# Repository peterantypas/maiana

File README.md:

# MAIANA&trade;: The Open Source AIS Transponder

I started this project around 2015 with the intention of experimenting and eventually building something for my own boat.
I was not impressed with commercial AIS class B transponders. They seemed bloated, expensive and some of them were particularly power-hungry. Also, my boat is rather small and I have very little room for "nav" instruments, so I didn't want a huge enclosure inside plus two external RF cables, one for VHF and one for GPS. So I set out to create my own "lean and mean" design and I sailed with it for 2 years.

Fast forward to 2023, and it has taken a life of its own:

The main difference between MAIANA&trade; and every commercial transponder is that it's a self-contained unit, and thus its performance is 100% repeatable. The entire transponder circuit, the GNSS and all antennas are in the same housing. The design has been validated by fabricating _over 300 units_ now (July 2023).

So with all the core functionality kept outside and under tight control, the only other thing we need is power and data connections. Now, what's the most common cable that can carry a few signals 50 feet away? If you guessed "Ethernet", you guessed right. Commonplace Cat5 cable can deliver power plus serial data signals anywhere on an average sized pleasure boat. So that's how the exterior unit connects to the cabin, where one of these breakouts offers USB, NMEA0183 or NMEA2000 adapters to connect to the rest of the boat's systems. 

## Hardware Design

### Mechanical
The antenna casing that you see in these photos is a piece of 1" Schedule 40 "furniture" grade PVC pipe. It is the highest grade of such material, with a solid white PVC core (not a coated household grade pipe). Still, it's the most inexpensive UV resistant material available, and it looks great too!

The VHF antenna whip is built using an epoxy wound filament tube coated with high quality, UV resistant irradiated polyolefin ("heat shrink"). The company that makes this tubing (and helped me with this design challenge) also built the landing gear for NASA's Ingenuity helicopter on Mars, so they definitely understand how to deal with harsh environments. The bottomline is that unlike typical fiberglass antenna masts, this antenna is not going to degrade and "blossom" under continuous UV exposure. Starting with January of 2022, the antenna tube will be made of two telescopic pieces of the same material. This will greatly reduce the cost of shipping the kit to Europe and Australia.

The entire outdoor assembly is held together by the same high grade heat shrink tubing, so there is no need for any adhesives! The main water seal is formed by heat shrinking around a specially designed 3D printed cap made of PLA. This part naturally softens when heated and as it's compressed by the heat shrink tubing surrounding it, it forms a permanent, watertight colar around the antenna tube. This blocks rain water and salt spray from the top. A layer of clear heat shrink in the interior forms a secondary water seal encompassing the lower part of the antenna. Finally, the PCB can be sprayed with conformal coating for an added layer of protection. Silicone spray works best and has no appreciable detuning effect on the GNSS.

With no adhesives getting in the way, the unit can actually be opened and serviced by (carefully) cutting through the heat shrink tubing with a knife, then resealing with the same material and method as before. This, in fact, was one of my design goals from the beginning.

### Electrical
As I mentioned already, the transponder circuit is inside the antenna case. It's a 24mm x 84mm 4-layer PCB:

The core design is based on two Silicon Labs "EZRadio Pro" series ICs. All kits shipping today are based on the Si4460.

The microcontroller on this board is a STM32L4 series (422, 431 and 432 supported). I chose these because the 80MHz clock allows the SPI bus to operate at exactly 10MHz which is the maximum supported by the Si446x ICs. This is important, as a transponder is a *hard real time* application, so SPI latency must be minimized. All kits today are based on the STM32L432KBU6.

The GNSS is now a Quectel L76L-M33 and relies on a Johansson ceramic chip antenna. It usually takes a minute to acquire a fix outdoors from a cold start. With the latest antenna tuning, it offers near-navigation grade accuracy (typical HDOP at sea is less than 2 meters).

The transmitter front end is based on a power MOSFET typically found in handheld VHF radios and outputs just over 2 Watts (+33dBm). It has a verified range of over 20 nautical miles on a masthead and 10+ miles on a pushpit.

The system is designed to run from a 12V battery and exposes a 3.3V-level UART for connecting to the rest of the boat. The UART continuously sends GPS and AIS data in NMEA0183 format at 38.4Kbps. It also accepts certain commands for management. The breakout boxes pictured above deliver this stream via USB, NME0183 (RS422) or NMEA 2000 (CAN). The 3 "fancy" breakouts feature _galvanic isolation_ of their USB connection to avoid causing unintended problems with laptops and other devices whose power supplies are meant to _float_. This also means that you cannot use USB to power MAIANA&trade; - it must connect to a 12V battery.

In addition, there is now a "bare bones" UART+USB breakout:

This provides the simplest, lowest cost interface to a Raspberry Pi, Arduino or any other similar system you may want to wire directly. It is _not_ galvanically isolated to keep the cost really low. This adapter is now part of the base kit and ships with every configuration.

For the circuit to transmit, it must be configured with persistent station data (MMSI, call sign, name, dimensions, etc). This is stored in an EEPROM and is provisioned over a USB/serial connection via a command line interface. If station data is not provisioned, the device will simply run as a 2 channel AIS + GNSS receiver.

SOTDMA synchronization is based on the very acurate 1 PPS signal from the GNSS and the UTC clock. MAIANA&trade; does not synchronize itself to other stations because practical experience revealed that it's literally the "Wild West" out there: There are *many* commercial class A systems in operation today with buggy time slot management, so the simplest solution is to not rely on any of them. That said, the design behaves as a "class B" so it will not attempt to reserve time slots. It will just transmit autonomously and independently, based on Clear Channel Assessment, at the schedule permitted for this class of device. 

All adapters (except the "bare bones" one) feature a *silent mode* switch to explicitly disable transmission. If you need this for the UART adapter, you can wire one yourself.

In terms of power consumption, the main board draws about 45mA from 12V in receive mode, and spikes up to 700mA during transmission (for only 27 milliseconds). The adapters add an extra 0.5mA - 25mA depending on choice. So MAIANA&trade;'s most power hungry configuration needs about 0.6 Watts, which is a lot less than a typical LED-based cabin light.

### Software

The transponder firmware is an [Eclipse CDT project](latest/Firmware/Transponder) that you could clone and build. The code is C++ with a BSP abstraction layer so you need to tweak bsp/bsp.hpp or define one of the required symbols in the preprocessor to build for different board revisions. It contains snippets of STM32Cube generated code, but is does not follow ST's "spaghetti" structure.

The NMEA2000 adapter also has its own separate [firmware project](latest/Firmware/NMEA2000Adapter).

As of December 2021, MAIANA&trade; is fully integrated into [OpenPlotter](https://openmarine.net/openplotter). This means that it can be provisioned and managed entirely from its graphical interface, including firmware updates. To accomplish this, I had to make both a hardware and a software change: 

- The hardware change was to reinstate the I2C EEPROM that I used in earlier designs. This was necessary because STM32 applications that are interrupt heavy cannot safely erase and write any pages in the same flash bank, as the *entire* bank gets locked. This means that the next interrupt may be unable to execute, thus causing the processor to hang until the watchdog resets it. Moving persistence to an EEPROM solves this problem.

- The software change was to dust off the original [bootloader](latest/Firmware/Bootloader) that I wrote years ago and make it bulletproof: Even if you manage to brick the unit by uploading garbage firmware into it, it has a built-in "rescue" mode. All you have to do is toggle the TX switch a couple of times during the first 2 seconds after power-up and it will enter firmware update mode again.

### CAD

Everything is [here](latest/CAD). 

### Building the unit

This is going to be difficult for all but the most technically advanced. The board features all surface mounted components, with 4 QFNs, a few SOT-363s and tightly spaced 0603 passives. The antenna switch on board 11.3.0 is about 0.8 x 1 mm and you'll need a microscope to align it. So unless you're very skilled and well equipped, you will find it difficult to build. 

### Buying a kit

I have developed a kit which includes pre-soldered (and programmed) boards as well as the antenna, main casing and heat shrink tubing. See [the installation manual here](https://github.com/peterantypas/maiana/blob/master/latest/Manuals/MAIANA%E2%84%A2%20Assembly%20Manual%20(Rev%204).pdf) to get a better idea of the process.

If you are located in North America, send an email to *maiana.kits@_dontspam_gmail.com* (remove the spambot blocker of course). Tariffs have made it difficult to ship to Europe and vice versa, so [OpenMarine](https://shop.openmarine.net) is working with European based teams to build and ship directly from Barcelona, Spain.

### License

CAD and transponder firmware are licensed under GPLV3. I chose the most "copyleft" license to discourage commercial entities from ripping this off and then "close-sourcing" it. The flipside of this is that if you can fork the design and make something better, then you deserve the success! That said, MAIANA&trade; will become a registered trademark soon, so if you plan to do this you must use a different name.

The NMEA2000 adapter firmware is under MIT license to be consistent with the libraries it depends on. Feel free to use it as you wish.

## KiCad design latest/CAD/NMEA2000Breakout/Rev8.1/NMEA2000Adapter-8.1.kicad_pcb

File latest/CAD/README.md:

## Board design files

This directory contains Eagle CAD files as well as schematic PDFs and Gerber exports for board fabrication.

The board stackup is good enough for either OSH Park 4-layer, or JLCPCB 4-layer with controlled impedance (JLC2313). 

### Latest Board

Revision 11.5.2 does away with the (hard to source) regulator from ST and replaces it with a Zener + NPN combination that delivers about 8.5V to the PA under load.

### Breakouts
These directories contain Eagle and FreeCAD files for the NMEA0183, NMEA 2000 and USB adapters. Their front panels are PCBs so gerbers are
here as well. The UART+USB adapter is a very basic breakout board for those who would rather wire the transponder themselves.

### Antenna
This directory contains FreeCAD and STEP exports of the 3D printed parts that make up the antenna.

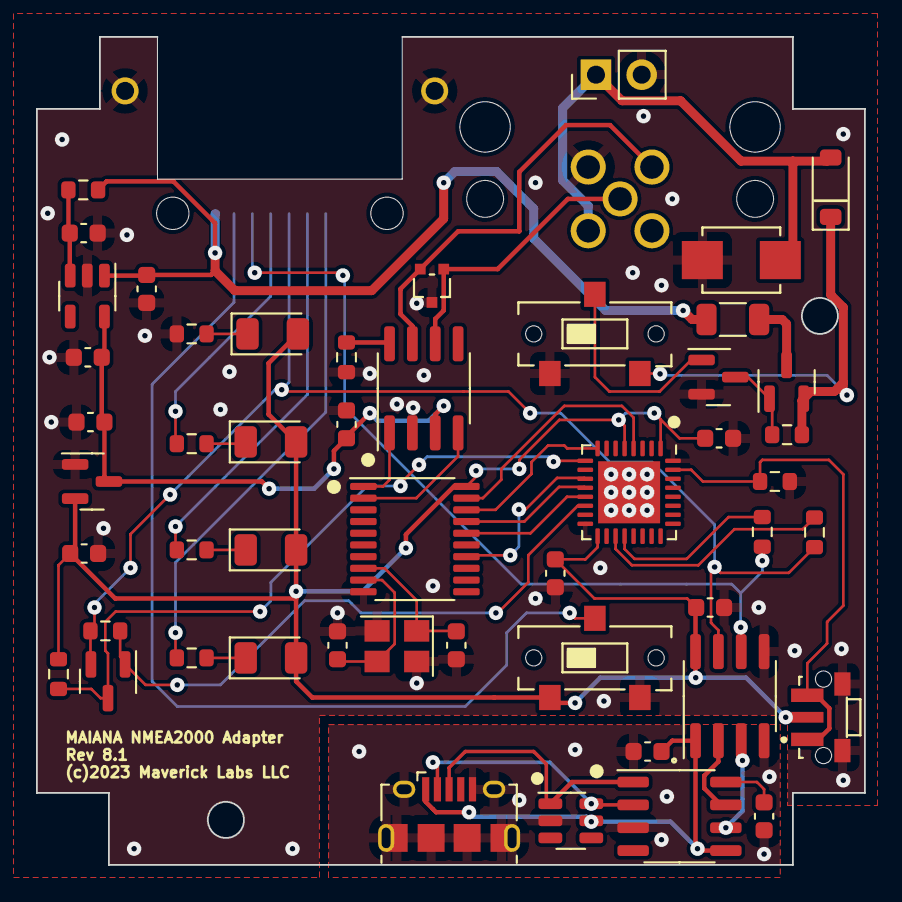
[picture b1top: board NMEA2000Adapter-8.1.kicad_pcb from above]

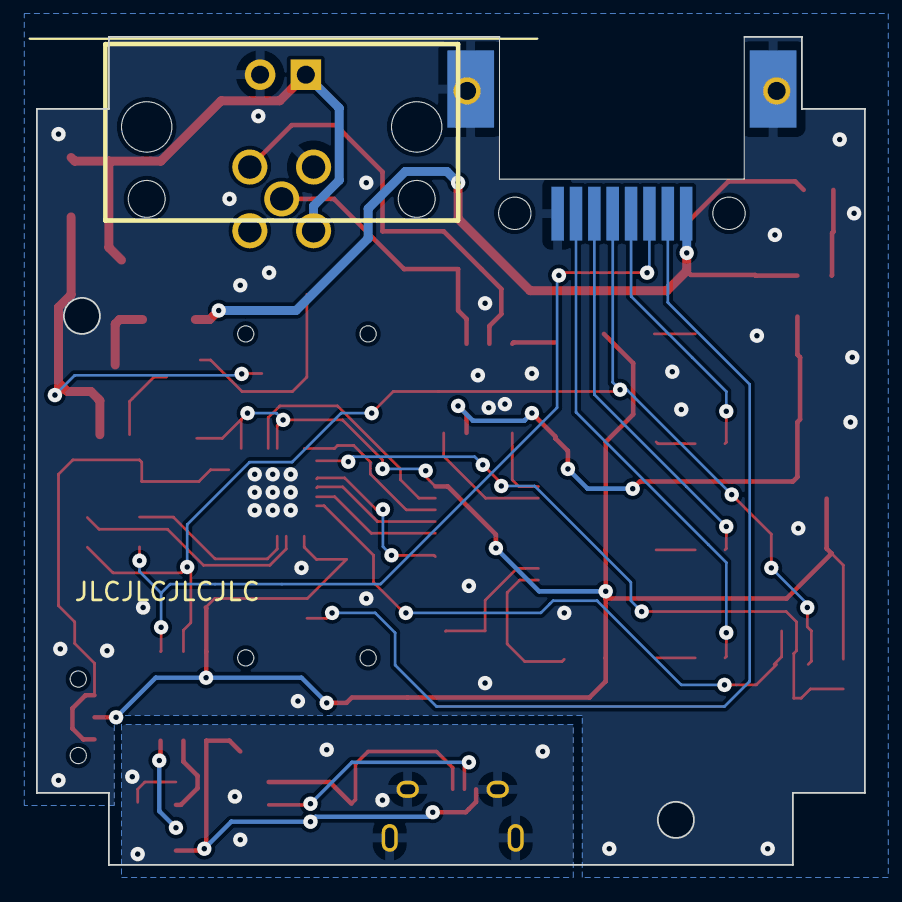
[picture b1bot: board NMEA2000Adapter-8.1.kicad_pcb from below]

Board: 2 copper layers, 46.0 x 46.0 mm, 52 parts (2 on the bottom side), 44 nets.

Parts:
C1, C2, C3, C11, C12, C13: 0.1uF; C_0603_1608Metric
C4, C5: 20pF; C_0603_1608Metric
C6, C7, C8, C9, C10: 1uF; C_0603_1608Metric
D1, D2, D3, D4: LED; LED_1206_3216Metric
D5: PESD1CAN-U; SOT323
D6: SMBJ16CA; DIOM4336X265N
D8: D_Schottky; D_SOD-123
J1: 12-3701-05; MICRO_C_5PIN
J2: RJ-82A86MMNL
J3: USB_B_Micro; USB_Micro-B_Amphenol_10118194_Horizontal
J4: Conn_01x02; PinHeader_1x02_P2.54mm_Vertical
Q1, Q3: BSS138; SOT-23
Q2: AO3401A; SOT-23
R1, R2, R3, R4: 2k2; R_0603_1608Metric
R5, R6, R7, R8, R9, R10: 10k; R_0603_1608Metric
R11, R12: 0R; R_0603_1608Metric
SW1, SW2: CL-SB-12B-01T
SW3: TS-1814; TE_1977066-1
TH1: BSMD1206-050-16V; R_1206_3216Metric
U1: STM32L432KBUx; QFN-32-1EP_5x5mm_P0.5mm_EP3.45x3.45mm
U2: MCP2515-xST; TSSOP-20_4.4x6.5mm_P0.65mm
U3: MCP2551-I-SN; SOIC-8_3.9x4.9mm_P1.27mm
U4: SRV05-4; SOT-23-6
U5: CH340N; SO-8_3.9x4.9mm_P1.27mm
U6: ISO7721DR; SOIC-8_3.9x4.9mm_P1.27mm
U7: TJ5205SF5-5.0; SOT-23-5
U8: SE8533X2-HF; SOT-23
Y1: X322516MOB4SI; Crystal_SMD_3225-4Pin_3.2x2.5mm

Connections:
+3.3V: C2.1, C10.1, C12.1, C13.1, D1.2 (A), D2.2 (A), D3.2 (A), D4.2 (A), R10.1, SW2.1, SW3.2, U1.1 (VDD), U1.5 (VDDA), U1.17 (VDD), U2.20 (VDD), U6.8 (VDD2), U8.2 (VO)
+5V: C8.1, C9.1, C11.1, U3.3 (VDD), U7.5 (OUT), U8.3 (VI)
+12V: D6.2, D8.2 (A), J1.2, J4.1
/CAN/CAN_H: D5.2, J1.4, U3.7 (CANH)
/CAN/CAN_L: D5.1, J1.5, U3.6 (CANL)
/CAN/NRST: U1.4 (NRST), U2.19 (~RESET)
/CAN/SPI_CS: U1.8 (PA2), U2.18 (~CS)
/CAN/SPI_MISO: U1.12 (PA6), U2.17 (SO)
/CAN/SPI_MOSI: U1.13 (PA7), U2.16 (SI)
/CAN/SPI_SCK: U1.11 (PA5), U2.14 (SCK)
/Connections/AIS_RX_EVENT: J2.P$6 (6), R3.2
/Connections/AIS_TX_EVENT: J2.P$7 (7), R4.2
/Connections/GPS_STATUS: J2.P$4 (4), R2.2
/Connections/MCU_UART_RX: R12.2, U1.20 (PA10)
/Connections/MCU_UART_TX: R11.2, U1.19 (PA9)
/Connections/TRANSPONDER_UART_TX: J2.P$5 (5), Q3.2 (S), R9.2, R11.1, U6.7 (VIA)
/Connections/TX_DISABLE: J2.P$2 (2), SW2.C
/Connections/V_OUT: C7.1, J2.P$1 (1), R6.1, TH1.1, U7.1 (IN)
/MCU/BOOT0: R8.1, SW3.1, SW3.3, U1.31 (PH3)
/Power/PWR_CTRL: Q1.1 (G), SW1.C
/Power/V_IN: D8.1 (K), Q2.2 (S), R5.1, SW1.3
CH340_RX: U5.7 (RX), U6.2 (VOA)
CH340_TX: U5.6 (TX), U6.3 (VIB)
D+: J3.3 (D+), U4.1 (IO1), U5.1 (D+)
D-: J3.2 (D-), U4.6 (IO4), U5.2 (D-)
GND: C2.2, C4.2, C5.2, C6.2, C7.2, C8.2, C9.2, C10.2, C11.2, C12.2, C13.2, D5.3, D6.1, J1.3, J2.P$8 (8), J2.P$9, J2.P$10, J2.P$11, J2.P$12, J4.2, Q1.2 (S), R1.2, R7.2, R8.2, SW1.1, SW2.3, SW3.S1 (SHIELD), SW3.S2 (SHIELD), U1.16 (VSS), U1.32 (VSS), U1.33 (VSS), U2.10 (VSS), U3.2 (VSS), U6.5 (GND2), U7.2 (GND), U8.1 (GND), Y1.2, Y1.4
GND2: C1.2, C3.2, J3.5 (GND), J3.6 (Shield), U4.2 (VN), U5.3 (GND), U6.4 (GND1)
NMEA_RX: Q3.3 (D), R10.2, U1.9 (PA3)
NMEA_RX_EN: Q3.1 (G), R9.1, U1.14 (PB0)
unnamed: D1.1 (K), R1.1
unnamed: D2.1 (K), R2.1
unnamed: D3.1 (K), R3.1
unnamed: D4.1 (K), R4.1
unnamed: Q1.3 (D), Q2.1 (G), R5.2
unnamed: Q2.3 (D), TH1.2
unnamed: U2.2 (RXCAN), U3.4 (RXD)
unnamed: U2.1 (TXCAN), U3.1 (TXD)
unnamed: R7.1, U3.8 (Rs)
unnamed: C1.1, U5.8 (V3)
unnamed: C6.1, R6.2, U7.3 (EN)
TRANSPONDER_UART_RX: J2.P$3 (3), R12.1, U6.6 (VOB)
VBUS: C3.1, J3.1 (VBUS), U4.5 (VP), U5.5 (VCC), U6.1 (VDD1)
XTL1: C5.1, U2.8 (OSC2), Y1.1
XTL2: C4.1, U2.9 (OSC1), Y1.3

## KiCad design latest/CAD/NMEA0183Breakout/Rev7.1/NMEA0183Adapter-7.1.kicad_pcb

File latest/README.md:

## This is the current version

This folder contains the latest and greatest. Under CAD/, you'll find directories for each board revision with associated Eagle files and exports. 

Under Firmware/ you'll find two Eclipse CDT projects. One for the transponder, and one for the NMEA 2000 adapter.

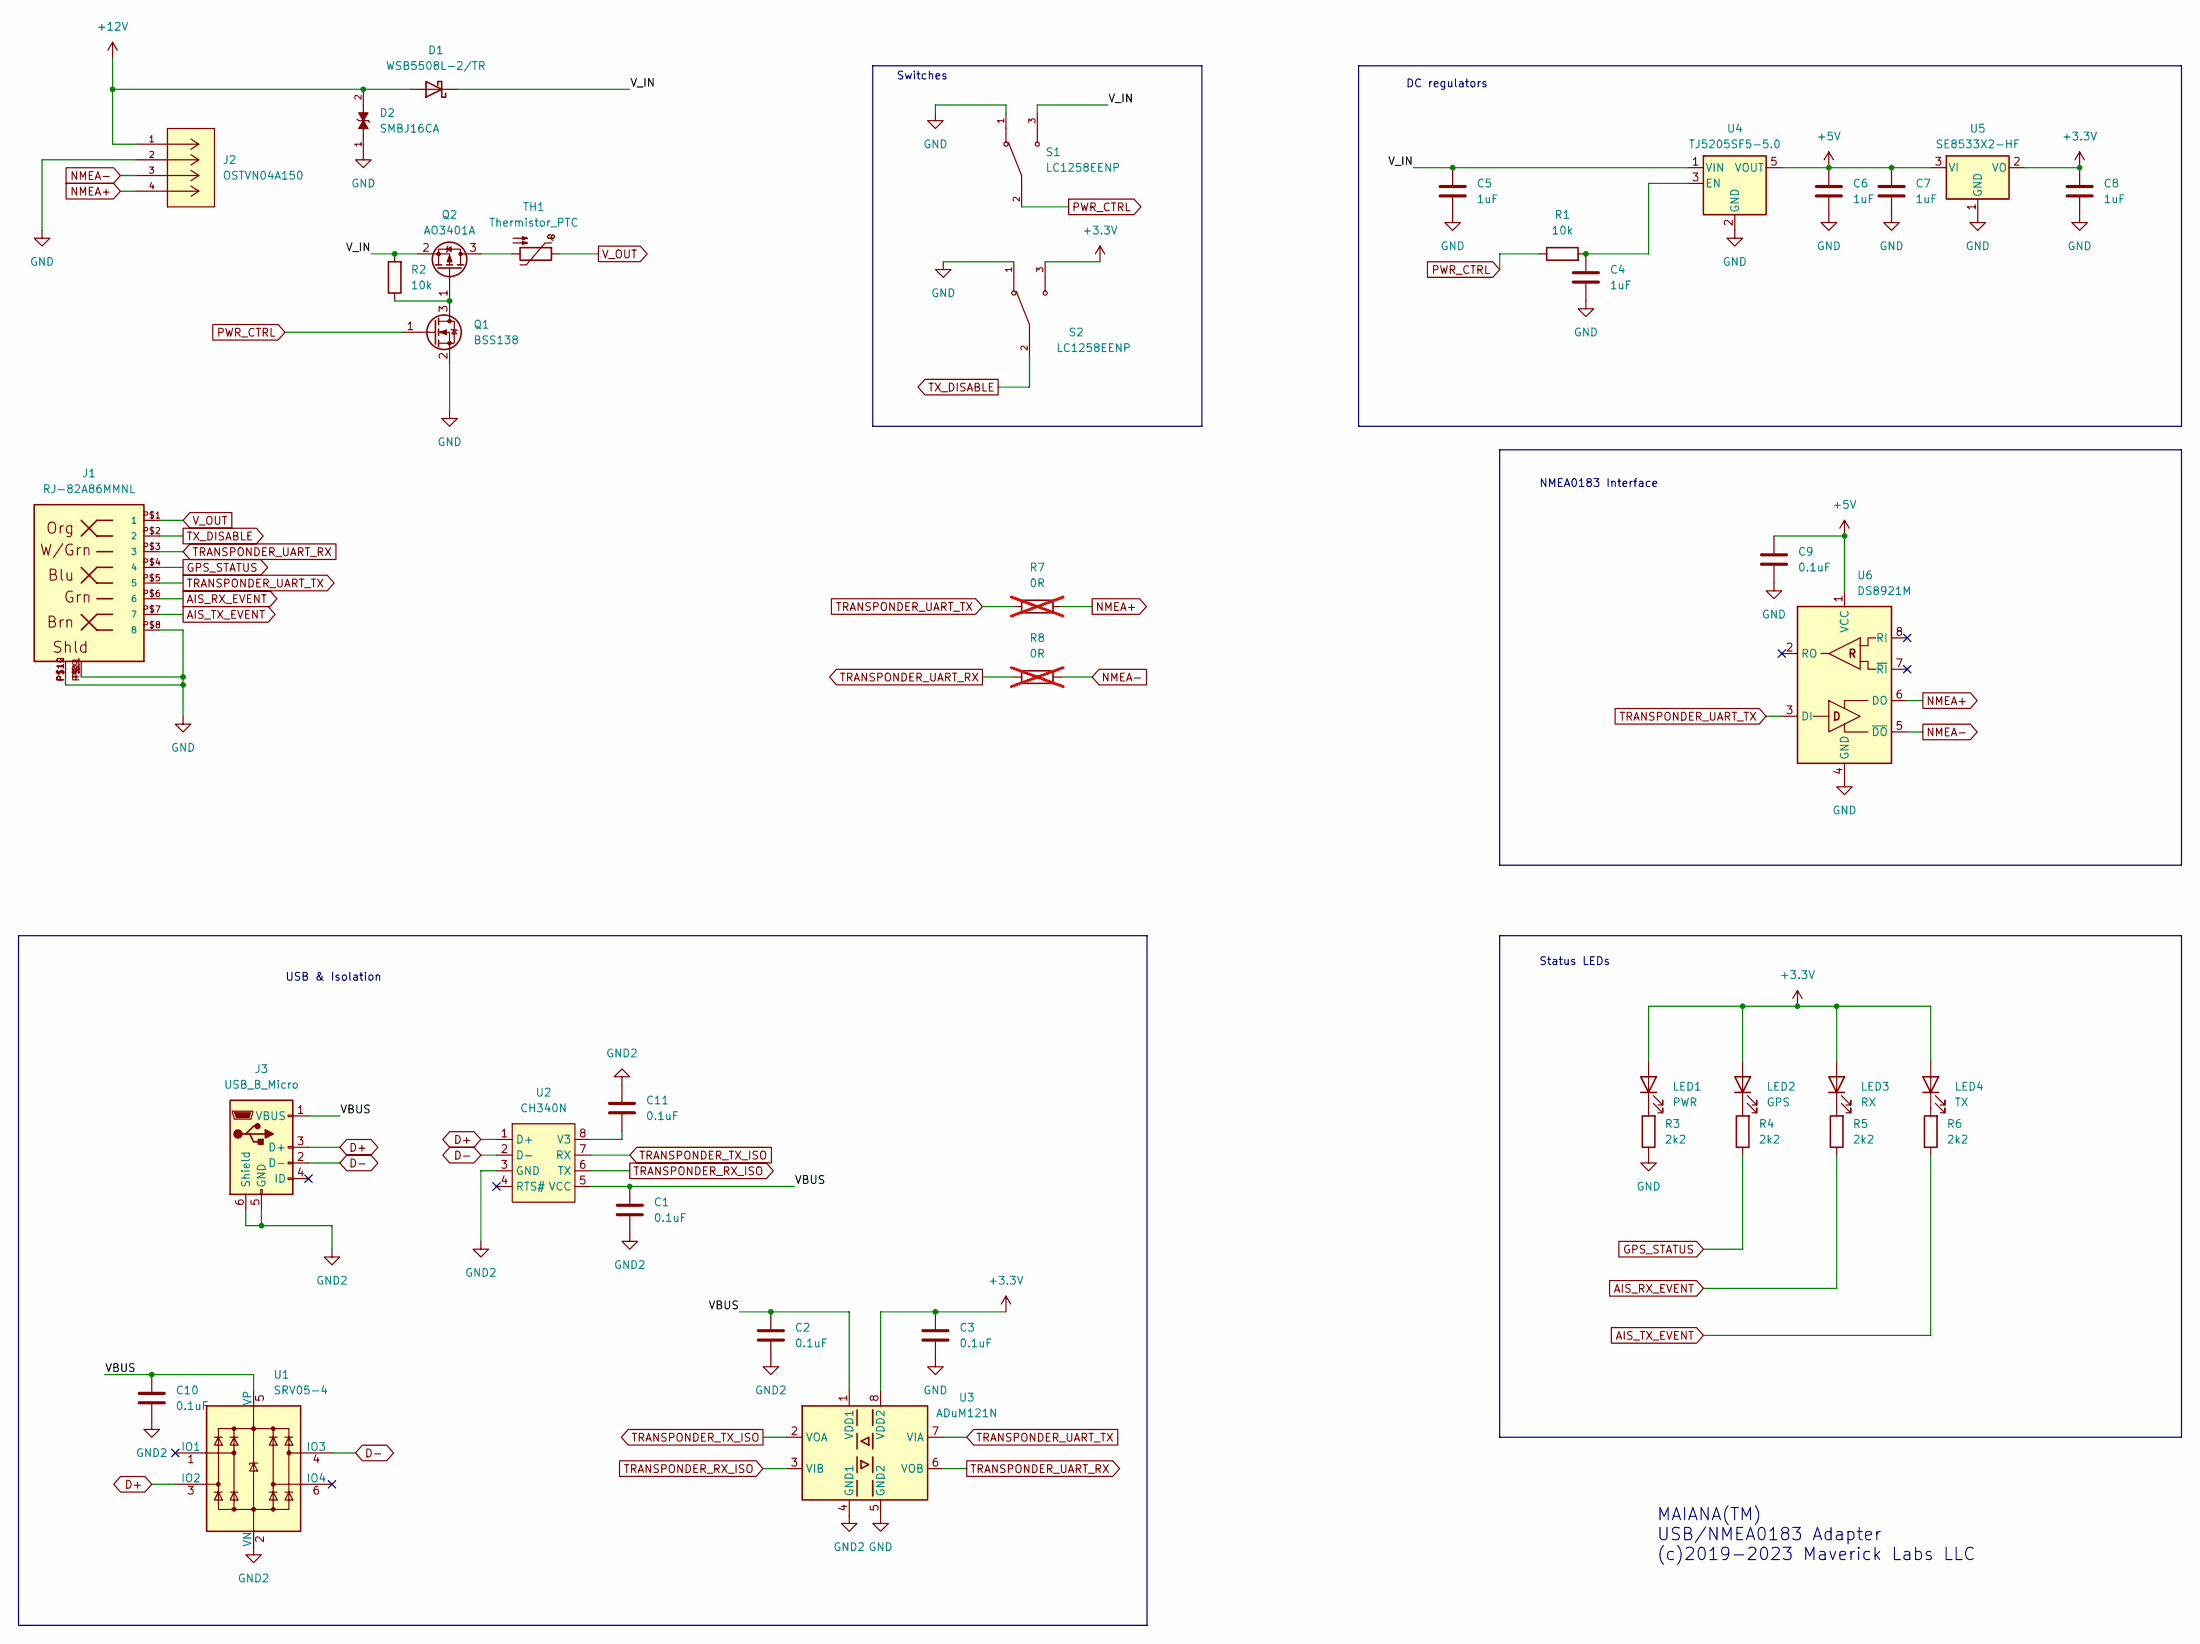
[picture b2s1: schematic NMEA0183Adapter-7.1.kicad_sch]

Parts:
C1, C2, C3, C9, C10, C11: 0.1uF; C_0603_1608Metric
C4, C5, C6, C7, C8: 1uF; C_0603_1608Metric
D1: WSB5508L-2/TR; D_SOD-123
D2: SMBJ16CA; DIOM4336X265N; PARTREV I2102
J1: RJ-82A86MMNL; PARTNO RJ-82A86MMNL
J2: OSTVN04A150; CONN_OSTVN04A150_OST; MANUFACTURER_PART_NUMBER OSTVN04A150; DIGI-KEY_PART_NUMBER_1 ED10563-ND
J3: USB_B_Micro; USB_Micro-B_Amphenol_10118194_Horizontal
LED1: PWR; LED_1206_3216Metric
LED2: GPS; LED_1206_3216Metric
LED3: RX; LED_1206_3216Metric
LED4: TX; LED_1206_3216Metric
Q1: BSS138; SOT-23
Q2: AO3401A; SOT-23
R1, R2: 10k; R_0603_1608Metric
R3, R4, R5, R6: 2k2; R_0603_1608Metric
R7, R8: 0R; R_0603_1608Metric; not fitted
S1, S2: LC1258EENP; SW_LC1258EENP; PARTREV C
TH1: Thermistor_PTC; R_1206_3216Metric
U1: SRV05-4; SOT-23-6
U2: CH340N; SO-8_3.9x4.9mm_P1.27mm
U3: ADuM121N; SOIC-8_3.9x4.9mm_P1.27mm
U4: TJ5205SF5-5.0; SOT-23-5
U5: SE8533X2-HF; SOT-23
U6: DS8921M; SOIC-8_3.9x4.9mm_P1.27mm

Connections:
+3.3V: C3.1, C8.1, LED1.2 (A), LED2.2 (A), LED3.2 (A), LED4.2 (A), S2.3, U3.8 (VDD2), U5.2 (VO)
+5V: C6.1, C7.1, C9.1, U4.5 (VOUT), U5.3 (VI), U6.1 (VCC)
+12V: D1.2 (A), D2.2, J2.1
/VBUS: C1.1, C2.1, C10.1, J3.1 (VBUS), U1.5 (VP), U2.5 (VCC), U3.1 (VDD1)
/V_IN: C5.1, D1.1 (K), Q2.2 (S), R2.2, S1.3, U4.1 (VIN)
AIS_RX_EVENT: J1.P$6 (6), R5.1
AIS_TX_EVENT: J1.P$7 (7), R6.1
D+: J3.3 (D+), U1.3 (IO2), U2.1 (D+)
D-: J3.2 (D-), U1.4 (IO3), U2.2 (D-)
GND: C3.2, C4.2, C5.2, C6.2, C7.2, C8.2, C9.2, D2.1, J1.P$8 (8), J1.P$9, J1.P$10, J1.P$11, J1.P$12, J2.2, Q1.2 (S), R3.1, S1.1, S2.1, U3.5 (GND2), U4.2 (GND), U5.1 (GND), U6.4 (GND)
GND2: C1.2, C2.2, C10.2, C11.1, J3.5 (GND), J3.6 (Shield), U1.2 (VN), U2.3 (GND), U3.4 (GND1)
GPS_STATUS: J1.P$4 (4), R4.1
NMEA+: J2.4, R7.1, U6.6 (DO)
NMEA-: J2.3, R8.1, U6.5 (~DO)
unnamed: LED1.1 (K), R3.2
unnamed: LED2.1 (K), R4.2
unnamed: LED3.1 (K), R5.2
unnamed: LED4.1 (K), R6.2
unnamed: Q1.3 (D), Q2.1 (G), R2.1
unnamed: Q2.3 (D), TH1.2
unnamed: C11.2, U2.8 (V3)
unnamed: C4.1, R1.2, U4.3 (EN)
PWR_CTRL: Q1.1 (G), R1.1, S1.2
TRANSPONDER_RX_ISO: U2.6 (TX), U3.3 (VIB)
TRANSPONDER_TX_ISO: U2.7 (RX), U3.2 (VOA)
TRANSPONDER_UART_RX: J1.P$3 (3), R8.2, U3.6 (VOB)
TRANSPONDER_UART_TX: J1.P$5 (5), R7.2, U3.7 (VIA), U6.3 (DI)
TX_DISABLE: J1.P$2 (2), S2.2
V_OUT: J1.P$1 (1), TH1.1

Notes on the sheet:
USB & Isolation
Status LEDs
MAIANA(TM) USB/NMEA0183 Adapter (c)2019-2023 Maverick Labs LLC
NMEA0183 Interface
DC regulators
Switches

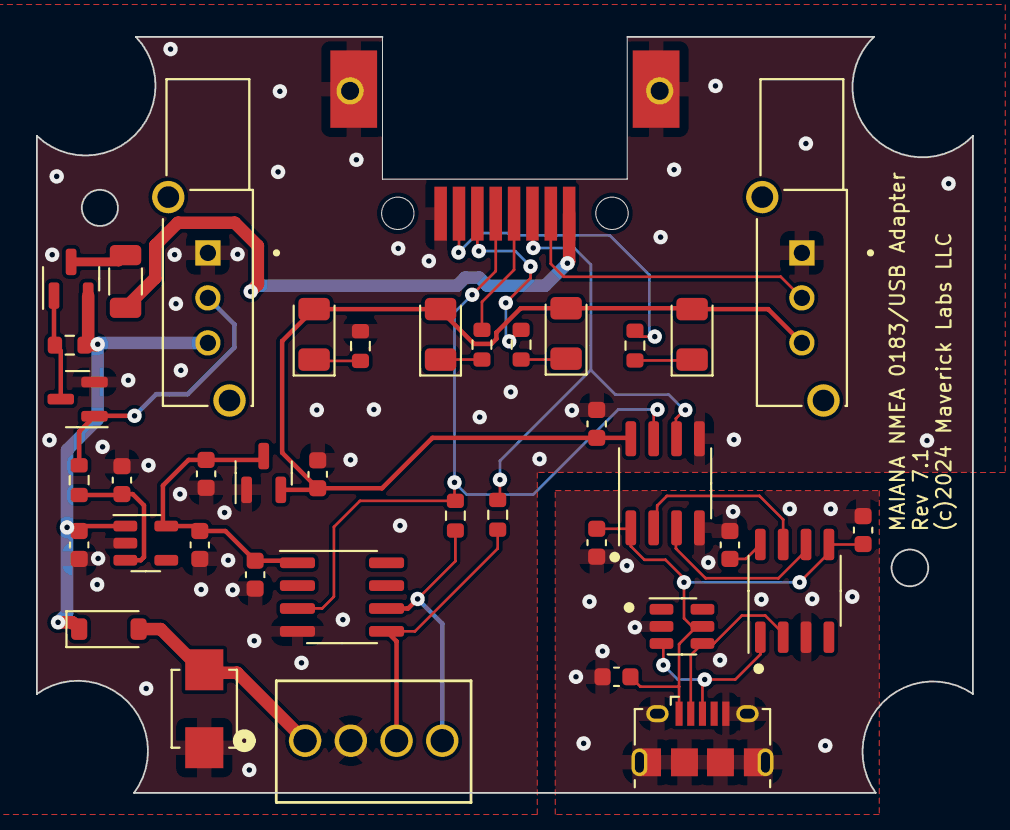
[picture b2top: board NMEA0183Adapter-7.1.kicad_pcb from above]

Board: 2 copper layers, 52.0 x 42.0 mm, 39 parts (0 on the bottom side), 29 nets.

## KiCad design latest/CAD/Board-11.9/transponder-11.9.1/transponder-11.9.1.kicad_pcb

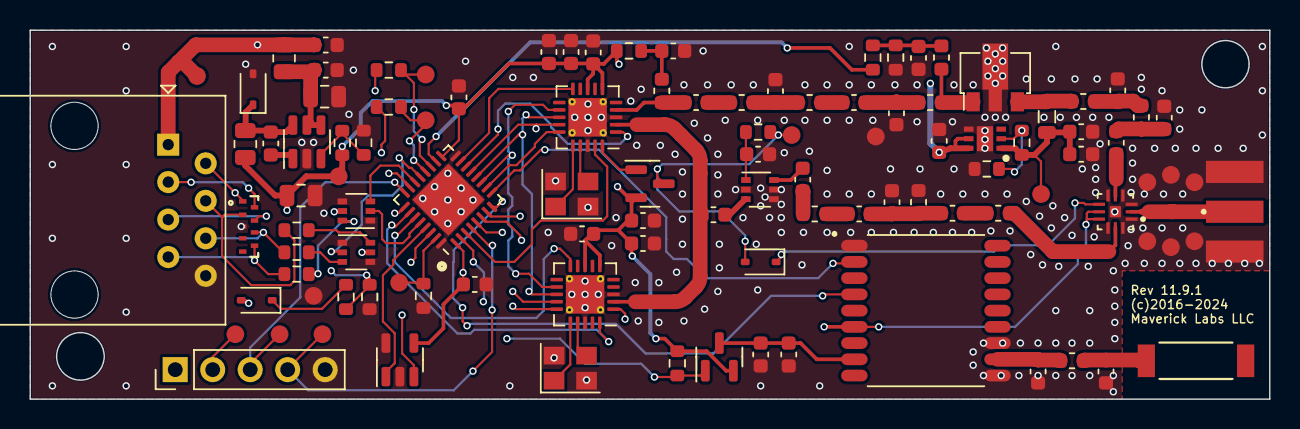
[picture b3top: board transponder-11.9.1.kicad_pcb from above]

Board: 4 copper layers, 84.0 x 25.0 mm, 109 parts (0 on the bottom side), 79 nets.

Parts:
AE1: 1575AT43A0040E; ANT_1575AT_JOT
C1, C2, C16, C18: 2.2nF; C_0603_1608Metric
C3, C9, C11, C19, C27, C31: 22nF; C_0603_1608Metric
C4, C5: 3.3pF; C_0603_1608Metric
C6, C8, C12: 91pF; C_0603_1608Metric
C7, C10, C23, C24, C30: 2.2uF; C_0603_1608Metric
C13, C20: 470pF; C_0603_1608Metric
C14, C17: 110pF; C_0603_1608Metric
C15: 36pF; C_0603_1608Metric
C21: 20pF; C_0603_1608Metric
C22: 16pF; C_0603_1608Metric
C25, C26, C34, C35: 0.1uf; C_0603_1608Metric
C28: 22uF; C_0805_2012Metric
C29: 10uF; C_0805_2012Metric
C32: 4pF; C_0603_1608Metric
C33: 2.2pF; C_0603_1608Metric
CR1: D3V3X8U9LP3810-7; U-DFN3810-9TYPE_B_DIO
D1, D3, D4: BAT54WS; D_SOD-323
IC1: LDFPVR; SON65P200X200X100-7N-D
J1: RJ45; RJ45_Amphenol_54602-x08_Horizontal
J2: Conn_01x05; PinHeader_1x05_P2.54mm_Vertical
J3: CON-SMA-EDGE-S; RFSOLUTIONS_CON-SMA-EDGE-S
L1, L2: 270nH; L_0603_1608Metric
L3: 10nH; L_0603_1608Metric
L4: 2.2uH; L_0805_2012Metric
L5: 13nH; L_0603_1608Metric
L6: 39nH; L_0603_1608Metric
L7: 20nH; L_0603_1608Metric
L8, L9: 470nH; L_0603_1608Metric
L10: 47nH; L_0603_1608Metric
L11: 68nH; L_0603_1608Metric
L12, L13: 4.7uH; R_0805_2012Metric
L14: 5.6nH; L_0603_1608Metric
Q1: AFT05MS004NT1; SOT-89-3
Q2, Q7: AO3401A; SOT-23
R1: 220R; R_0603_1608Metric
R2, R6, R9, R10, R11: 10k; R_0603_1608Metric
R3: 3k3; R_0603_1608Metric
R4: 22R; R_0603_1608Metric
R5: 47k; R_0603_1608Metric
R7: 51k; R_0603_1608Metric
R8: 16k; R_0603_1608Metric
R12, R13, R17: 1k1; R_0603_1608Metric
R14, R15, R16: 100R; R_0603_1608Metric
TP1: TP_1.0MM
TP2, TP3, TP4, TP5, TP6, TP7, TP8, TP9, TP10, TP11, TP12, TP13, TP14, TP15, TP16, TP17, TP18, TP19: TP_1.2MM
U1, U2: Si4460; QFN-20-1EP_4x4mm_P0.5mm_EP2.6x2.6mm_ThermalVias
U3: BGA2800,115; SOT-363_SC-70-6
U4: L76L-M33; XCVR_L76L-M33
U5: STM32L432KBUx; QFN-32-1EP_5x5mm_P0.5mm_EP3.45x3.45mm
U6: AP3211K; SOT-23-6
U7: 24LC01BT/OT; SOT-23-5
U8: SKY13330-397LF; QFN50P200X200X65-13N
U9, U10: SI1926DL-T1-E3; SOT-363_SC-70-6
Y1, Y2: ECS-300-10-33B-CKM-TR; Crystal_SMD_3225-4Pin_3.2x2.5mm

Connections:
+3.3V: C7.2, C8.2, C9.2, C10.2, C11.2, C12.2, C28.1, C34.2, C35.2, J2.1, L12.2, Q2.2 (S), Q7.2 (S), R4.1, R7.1, R9.1, TP8.1, U1.6 (VDD), U1.8 (VDD), U2.6 (VDD), U2.8 (VDD), U4.6 (V_BCKP), U5.1 (VDD), U5.5 (VDDA), U5.17 (VDD), U7.4 (V_{CC}), U8.8 (EN), U8.9 (VCC)
/Connections/GPS_STATUS: U5.21 (PA11), U9.2 (G1)
/Connections/HOST_GPS_STATUS: CR1.2, J1.4, R14.1
/Connections/HOST_RX_STATUS: CR1.7, J1.6, R15.1
/Connections/HOST_TX_OFF: CR1.1, D3.2 (A), J1.2
/Connections/HOST_TX_STATUS: CR1.6, J1.7, R16.1
/Connections/HOST_UART_RX: CR1.8, J1.5, R12.1
/Connections/HOST_UART_TX: CR1.9, J1.3, R13.1
/Connections/MCU_TX_OFF: U5.22 (PA12), U10.3 (D2)
/Connections/MCU_UART_RX: R13.2, TP12.1, U5.20 (PA10)
/Connections/MCU_UART_TX: R12.2, TP11.1, U5.19 (PA9)
/Connections/RX_STATUS: U5.7 (PA1), U9.5 (G2)
/Connections/TX_STATUS: U5.28 (PB5), U10.2 (G1)
/Connections/V_IN: C24.2, C25.2, IC1.5 (EN), IC1.6 (VIN), J1.1, L13.1, TP10.1
/GNSS/GPS_1PPS: U4.4 (1PPS), U5.8 (PA2)
/GNSS/GPS_EN: Q2.1 (G), R9.2, U5.2 (PC14)
/GNSS/GPS_OUT: U4.2 (TXD1), U5.9 (PA3)
/MCU/RX_CLK: U2.20 (GPIO3), U5.26 (PB3)
/MCU/RX_CS: U2.15 (~SEL), U5.6 (PA0)
/MCU/RX_DATA: U2.10 (GPIO1), U5.27 (PB4)
/MCU/RX_SDN: U2.1 (SDN), U5.25 (PA15)
/MCU/SPI_MISO: U1.13 (SDO), U2.13 (SDO), U5.12 (PA6)
/MCU/SPI_MOSI: U1.14 (SDI), U2.14 (SDI), U5.13 (PA7)
/MCU/SPI_SCK: U1.12 (SCLK), U2.12 (SCLK), U5.11 (PA5)
/MCU/TRX_CKL: U1.19 (GPIO2), U5.3 (PC15)
/MCU/TRX_CS: U1.15 (~SEL), U5.10 (PA4)
/MCU/TRX_DATA: U1.10 (GPIO1), U5.15 (PB1)
/MCU/TRX_SDN: U1.1 (SDN), U5.14 (PB0)
/MCU/V_PA_BIAS: R3.1, U5.18 (PA8)
/Power/V_PA: C13.2, C23.2, IC1.1 (VOUT), L4.1, R5.1, TP9.1
/Receiver/RF_IN: L2.2, U8.11 (RF2)
/Receiver/TRX_OUT: C21.1, L9.1, U1.4 (TX)
/Receiver/V_LNA: D4.2 (A), Q7.3 (D), R1.1, TP13.1
GND: C3.2, C6.1, C7.1, C8.1, C9.1, C10.1, C11.1, C12.1, C13.1, C14.1, C15.1, C17.1, C19.1, C20.1, C22.1, C23.1, C24.1, C25.1, C26.1, C28.2, C29.2, C30.1, C31.1, C32.1, C33.1, C34.1, C35.1, CR1.3, D1.2 (A), IC1.4 (GND_1), IC1.7 (GND_2), J1.8, J2.5, J3.G1, J3.G2, J3.G3, J3.G4, L3.1, Q1.2 (S), R2.2, R6.2, R8.2, R10.2, R11.2, TP2.1, TP3.1, TP4.1, TP5.1, TP6.1, TP7.1, TP18.1, TP19.1, U1.3 (RXn), U1.18 (GND), U1.21 (GND), U2.3 (RXn), U2.18 (GND), U2.21 (GND), U3.2 (G), U3.4 (G), U3.5 (G), U4.1 (GND), U4.10 (GND), U4.12 (GND), U5.16 (VSS), U5.32 (VSS), U5.33 (VSS), U6.2 (GND), U7.2 (V_{SS}), U7.5 (WP), U8.1 (GND), U8.3 (GND), U8.4 (GND), U8.6 (GND), U8.10 (GND), U8.12 (GND), U8.13 (GND), U9.1 (S1), U9.4 (S2), U10.1 (S1), U10.4 (S2), Y1.2, Y1.4, Y2.2, Y2.4
NRST: J2.4, TP17.1, U5.4 (NRST)
unnamed: AE1.1, C33.2, L14.1
unnamed: C1.2, U3.3
unnamed: C2.1, U3.6
unnamed: C2.2, L1.1
unnamed: C4.1, C5.1, C6.2, L3.2
unnamed: C4.2, L1.2
unnamed: C5.2, L2.1
unnamed: C14.2, L5.2, L6.1
unnamed: C15.2, C16.1, L6.2
unnamed: C17.2, C18.2, L7.1
unnamed: C18.1, L11.2
unnamed: C19.2, L8.2, R2.1, R3.2
unnamed: C20.2, L9.2, R4.2
unnamed: C21.2, L10.1
unnamed: C22.2, L10.2, L11.1
unnamed: C27.2, D1.1 (K), L12.1, U6.6 (SW)
unnamed: D3.1 (K), R17.2
unnamed: D4.1 (K), U8.7 (CTRL)
unnamed: IC1.2 (ADJ/NC), R5.2, R6.1
unnamed: L4.2, L5.1, Q1.3 (D)
unnamed: L7.2, L8.1, Q1.1 (G)
unnamed: C30.2, C31.2, Q2.3 (D), U4.8 (VCC)
unnamed: Q7.1 (G), U1.20 (GPIO3)
unnamed: J3.1, TP1.1, U8.2 (RF1)
unnamed: R10.1, TP14.1, U5.31 (PH3)
unnamed: C1.1, U1.2 (RXp), U2.2 (RXp)
unnamed: U1.17 (XIN), Y1.3
unnamed: U1.16 (XOUT), Y1.1
unnamed: U2.17 (XIN), Y2.3
unnamed: U2.16 (XOUT), Y2.1
unnamed: C3.1, R1.2, U3.1 (Vcc)
unnamed: C32.2, L14.2, U4.11 (RF_IN)
unnamed: U5.29 (PB6), U7.1 (SCL)
unnamed: U5.30 (PB7), U7.3 (SDA)
unnamed: C27.1, U6.1 (BS)
unnamed: C26.2, C29.1, L13.2, U6.4 (EN), U6.5 (IN)
unnamed: R7.2, R8.1, U6.3 (FB)
unnamed: R14.2, U9.6 (D1)
unnamed: R15.2, U9.3 (D2)
unnamed: R16.2, U10.6 (D1)
unnamed: R11.1, R17.1, U10.5 (G2)
PA_OUT: C16.2, U8.5 (RF3)
SWCLK: J2.3, TP16.1, U5.24 (PA14)
SWDIO: J2.2, TP15.1, U5.23 (PA13)

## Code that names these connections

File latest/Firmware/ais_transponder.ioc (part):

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Mcu.Name=STM32L432K(B-C)Ux
Mcu.Package=UFQFPN32
Mcu.UserName=STM32L432KBUx
PA0-CK_IN.Signal=GPIO_Output
PA1.Signal=GPIO_Input
PA10.GPIOParameters=GPIO_Speed
PA10.GPIO_Speed=GPIO_SPEED_FREQ_MEDIUM
PA10.Mode=Asynchronous
PA10.Signal=USART1_RX
PA11.Signal=GPIO_Input
PA13\ (JTMS-SWDIO).Mode=Serial_Wire
PA13\ (JTMS-SWDIO).Signal=SYS_JTMS-SWDIO
PA14\ (JTCK-SWCLK).Mode=Serial_Wire
PA14\ (JTCK-SWCLK).Signal=SYS_JTCK-SWCLK
PA15\ (JTDI).Signal=GPIO_Output
PA2.GPIOParameters=GPIO_ModeDefaultEXTI
PA2.GPIO_ModeDefaultEXTI=GPIO_MODE_IT_RISING_FALLING
PA2.Signal=GPXTI2
PA3.Signal=USART2_RX
PA4.Signal=GPIO_Output
PA5.Mode=Full_Duplex_Master
PA5.Signal=SPI1_SCK
PA6.Mode=Full_Duplex_Master
PA6.Signal=SPI1_MISO
PA7.Mode=Full_Duplex_Master
PA7.Signal=SPI1_MOSI
PA8.Signal=GPIO_Input
PA9.GPIOParameters=GPIO_Speed
PA9.GPIO_Speed=GPIO_SPEED_FREQ_MEDIUM
PA9.Mode=Asynchronous
PA9.Signal=USART1_TX
PB0.Signal=GPIO_Output
PB1.Signal=GPIO_Input
PB3\ (JTDO-TRACESWO).Signal=GPIO_Input
PB4\ (NJTRST).Signal=GPIO_Input
PC14-OSC32_IN\ (PC14).Signal=GPIO_Output
PC15-OSC32_OUT\ (PC15).Signal=GPIO_Output
RCC.HSE_VALUE=8000000
RCC.SYSCLKFreq_VALUE=80000000
RCC.SYSCLKSource=RCC_SYSCLKSOURCE_PLLCLK
board=ais_transponder

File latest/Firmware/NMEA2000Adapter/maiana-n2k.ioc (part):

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Mcu.Name=STM32L422KBUx
Mcu.Package=UFQFPN32
Mcu.UserName=STM32L422KBUx
PA10.Mode=Asynchronous
PA10.Signal=USART1_RX
PA13\ (JTMS/SWDIO).Mode=Serial_Wire
PA13\ (JTMS/SWDIO).Signal=SYS_JTMS-SWDIO
PA14\ (JTCK/SWCLK).Mode=Serial_Wire
PA14\ (JTCK/SWCLK).Signal=SYS_JTCK-SWCLK
PA2.GPIOParameters=PinState,GPIO_Label,GPIO_ModeDefaultOutputPP
PA2.GPIO_Label=SPI1_CS
PA2.GPIO_ModeDefaultOutputPP=GPIO_MODE_OUTPUT_PP
PA2.PinState=GPIO_PIN_SET
PA2.Signal=GPIO_Output
PA4.GPIOParameters=PinState,GPIO_Label,GPIO_ModeDefaultOutputPP
PA4.GPIO_Label=CAN_RST
PA4.GPIO_ModeDefaultOutputPP=GPIO_MODE_OUTPUT_OD
PA4.PinState=GPIO_PIN_SET
PA4.Signal=GPIO_Output
PA5.Mode=Full_Duplex_Master
PA5.Signal=SPI1_SCK
PA6.Mode=Full_Duplex_Master
PA6.Signal=SPI1_MISO
PA7.Mode=Full_Duplex_Master
PA7.Signal=SPI1_MOSI
PA9.Mode=Asynchronous
PA9.Signal=USART1_TX
PB0.Signal=GPXTI0
PB6.Mode=I2C
PB6.Signal=I2C1_SCL
PB7.Mode=I2C
PB7.Signal=I2C1_SDA
RCC.HSE_VALUE=8000000
RCC.SYSCLKFreq_VALUE=80000000
RCC.SYSCLKSource=RCC_SYSCLKSOURCE_PLLCLK
board=custom

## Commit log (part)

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2020-10-03 Image
2020-10-03 License
2020-10-03 Photo2
2020-10-03 Initial commit / transfer from bitbucket
2020-10-03 Initial code commit
2020-10-03 Added Eagle CAD files
2020-10-03 Cleanup
2020-10-03 Schematic for 5.2
2020-10-03 Schematic for 6.1
2020-10-03 README tweak
2020-10-03 Switched default build to board 6.x
2020-10-03 Board 6.1.1
2020-10-03 README for Python script
2020-10-03 README in Firmware/
2020-10-03 More README
2020-10-04 Gerbers
2020-10-06 Build support for L412 (untested)
2020-10-07 Board 6.2.0
2020-10-07 Proper support for L412 MCU
2020-10-07 Comments in schematic
2020-10-08 README again
2020-10-08 Tweaked
2020-10-08 Board 6.2 tweak
2020-10-08 Transceiver tweak
2020-10-08 Checkpoint
2020-10-08 Memory overflow bug
2020-10-09 FUBAR
2020-10-09 First running port
2020-10-09 Watchdog
2020-10-10 Removed board 6.2
2020-10-13 Broken
2020-10-13 Board 6.1.0 bringup
2020-10-13 TX_OFF switch works now
2020-10-13 DFU logic moved to BSP
2020-10-17 RJ45 Breakout
2020-10-17 Removed 6.2
2020-10-17 Gerbers and schematic for breakout
2020-10-18 Tentatively adding board 7.0.x
2020-10-18 README
2020-10-18 7.x gerbers
2020-10-18 7.x assembly variants
2020-10-18 Updated photo
2020-10-19 Introduced 'blink' BSP functions
2020-10-19 BSP backward compatibility
2020-10-19 Removing Board 4.3
2020-10-23 Removed unused events
2020-10-23 Removed obsolete code
2020-11-02 Hard-coded noise floor for now
2020-11-02 Checkpoint before changing NF detection
2020-11-02 Overhaul of NF detector
2020-11-02 Corrected IRQ priorities
2020-11-02 Working, push is 4x faster
2020-11-02 No profiling
2020-11-03 RXPacket pool
2020-11-03 Profiling
2020-11-03 Validated good RX performance
2020-11-03 Checkpoint. Best RX performance possible with current architecture
2020-11-03 Removed profiling
2020-11-03 Reduced RSSI sampling to improve RX yield
2020-11-04 Checkpoint before changing START_RX implementation
2020-11-04 onBitClock() rarely runs over 104us now
2020-11-04 Good enough
2020-11-04 That wasn't a bare metal build :(
2020-11-04 Minor optimization
2020-11-21 Board 9.3
2020-11-21 Board 9.3 CAD
2020-11-21 9.3 photo
2020-11-25 Build issue w/ different SDKs
2020-11-30 More photos
2020-12-05 Corrected some transmitted fields
2020-12-11 Starting work on Si4362
2020-12-11 Appears to be detecting Si4463
2020-12-12 BSP for 10.x
2020-12-12 Fixed huge bug in command processor
2020-12-13 Board 10.x
2020-12-13 Board 10
2020-12-13 Introduced 'quiet' CLI mode for programming station data
2020-12-14 Flash persistence
2020-12-14 Removed FreeRTOS
2020-12-21 Crude, but working
2020-12-21 Chip-specific config headers
2020-12-25 Restored original CCA headroom, fixed GPIO config for RX IC
2020-12-25 Missing include
2020-12-25 Fixed message 24 encoding bug
2020-12-25 Deployed to boat
2020-12-25 Ejecting language.settings.xml from git
2020-12-25 Board 10.0.1
2020-12-25 10.0.1 schematic
2020-12-25 10.0.1 gerber update
2020-12-26 BSP cleanup
2020-12-27 Minor cleanup
2021-01-30 Fixed issue #46
2021-02-26 Resetting MCU every hour
2021-03-09 Untested support for STM32L422xx
2021-03-20 config and bsp for 10.5.0
2021-03-30 Board 10.5
2021-04-30 BSP 10.5
2021-05-05 L422 + gitignore
2021-05-24 Support for board 10.5/6 and 10.7
2021-05-31 BSP fixes
2021-06-01 Board 10.5.x CAD files
2021-06-05 10.5.0 BOM
2021-06-05 BSP cleanup + LEDManager
2021-06-27 Board 10.9 bringup
2021-07-10 Board 10.9 Finished
2021-07-11 Updated CAD
2021-07-11 More CAD
2021-07-11 Fill bits was incorrectly set to 0 on all single frame messages
2021-07-24 Project cleanup
2021-07-30 Project restructuring
2021-07-30 Placeholder
2021-07-30 NMEA 2000 Adapter FW
2021-07-30 FreeCAD for 0183 box
2021-08-04 N2K breakout final
2021-08-06 Manuals
2021-08-21 BSP for board 11.0
2021-08-24 Board 11.0 bringup complete
2021-08-27 GNSS should be off by default
2021-08-27 Board 11.0 final
2021-08-29 Enabled watchdog for N2k adapter
2021-09-09 Renamed folder
2021-09-20 Updated manuals
2021-09-20 Manual correction
2021-09-23 Initial changes for OP
2021-09-23 sentence
2021-09-23 TX LED logic 100% in FW
2021-09-27 OpenPlotter commands
2021-09-28 Small optimizations
2021-10-04 Legacy breakout support
2021-10-04 Cherry picked support for new/legacy breakouts
2021-10-04 Better way to mange TX LED
2021-10-12 Persistence delegated to BSP again
2021-10-12 Preliminary support for i2c EEPROM
2021-10-12 Migrate from flash to EEPROM
2021-10-13 Correct noise floor limit
2021-10-20 Board 11.3.0 is it
2021-10-20 FW rev 3.3.0
2021-10-20 Board 11.3 & UART breakout
2021-10-20 UART breakout photo
2021-10-23 Improved RX for Si4463
2021-10-25 New manuals
2021-10-29 GPS LED wasn't turning off after loss of fix
2021-11-03 Correction for Issue #88
2021-11-09 Increased robustness of FW update
2021-11-11 L432 build
2021-11-11 Build flags for L432
2021-11-12 New system information fields in
2021-11-12 Fixed huge regression bug
2021-11-12 v3.3.3
2021-11-13 FW update manual
2021-11-15 Brought back an old bootloader from the cold
2021-11-15 Bootloader-compatible build variants
2021-11-15 Bootloader flashes LEDs
2021-11-15 Release 4.0.0
2021-11-17 Python3 script for new bootloader
2021-11-17 Update README.md
    README update
2021-11-19 N2K adapter schematic
2021-11-19 N2K adapter gerbers
2021-11-19 N2K adapter Eagle files
2021-11-29 Fixed backward compatibility bug with legacy bootloader
2021-12-03 Delete system.tmp
    Deleted .tmp file
2021-12-03 Delete license.tmp
    Deleted .tmp file
2021-12-08 Updated USB breakout CAD
2021-12-08 Updated NMEA0183 breakout
2021-12-28 New UART+USB breakout
2021-12-28 Antenna parts
2021-12-28 Board 11.5.2
2021-12-28 Adapter image
2021-12-31 Add files via upload
    Fixed manual
2022-01-28 Checkpoint 2
2022-01-30 Improved robustness
2022-01-30 Fully functional but needs a lot of hardening
2022-01-30 Can detect DFU mode upon connecting
2022-02-03 Alpha version of WX app
2022-02-11 Fixed BSP for board 11.0
2022-02-12 New N2K adapter board
2022-02-14 GUI client validating HW revision
2022-02-20 align labels right
2022-02-21 New label alignment
2022-02-21 Fixed MAIANA Python client for Mac OS
2022-02-22 fixes for sizing and alignment
2022-02-24 Retuning for ECS crystal
2022-02-24 Fixed UI to enable FW update when board boots in 'rescue' mode
2022-02-24 Retuned for ECS crystal
2022-02-24 Another GUI bugfix
2022-02-24 GUI version 3.0
2022-02-24 GUI version 0.3
2022-03-01 .gitignore
2022-03-01 Binaries
2022-03-11 Board 7
2022-04-28 Latest n2k adapter CAD
2022-05-10 Board 11.8.0
2022-06-28 L432 support in N2K adapter
2022-12-03 Initial check-in for WiFi adapter
2022-12-04 Initial web server
2022-12-04 Main web page done
2022-12-04 Added all core pages
2022-12-05 Cleaned up http handlers
2022-12-05 Refactored HTTP handlers
2022-12-06 First functioning form
2022-12-06 Button reset logic
2022-12-07 NMEA gateway configuration
2022-12-07 Refactored CSS
2022-12-07 Refactoring and NMEA gateway skeleton
2022-12-08 Successful basic TCP server
2022-12-11 UDP sender
2022-12-11 WiFi station config works
2022-12-11 WiFi rollback, auto reboot on update
2022-12-11 NMEA gateway mode changes immediately
2022-12-12 AIS form retrieves data
2022-12-12 AIS configuration working
2022-12-13 Displaying HW and FW revs on main page
2023-01-16 Adding sdkconfig
2023-01-17 Factory reset
2023-03-01 Support for 10.0.1
    Regression for support of latest software on board 10.0.1
    Essentially it boils down to sense of the GPS_EN line and RX_EN line
2023-03-11 Fixed GPIO handling
2023-04-25 Abandoning for now
2023-04-29 Fixed some builds
2023-05-03 Abandoning
2023-06-19 Leaving this branch alone
2023-09-10 Updated installation manual
2023-09-13 Added bootloader binaries
2023-09-27 Detecting RF IC initialization error
2024-01-25 Board 11.9.0
2024-02-03 Board 11.9.1
2024-02-13 Initial build for 64K flash
2024-02-16 First build with L412 on 11.8.0
2024-02-16 New binaries
2024-02-17 Removed 11.9.0
2024-03-11 Initial testing of XO trimming CLI
2024-03-11 4.4.0
2024-03-11 Removed build directory
2024-03-11 Added 4.4.0 binary
2024-04-01 Fixed MCU reporting in CLI
2024-04-01 Added 4.4.1 binary
2024-06-15 Added 4.4.1 binary for L432 boards
2024-11-20 Reset '1' count after bitstuffing.
2025-01-29 KiCad projects for N2K and 0183 adapters
2025-07-09 Fixed build under GCC 13+
2026-04-29 feat: optional external GPS via USART1 (extgps on/off)
    Adds an opt-in feature that lets the transponder source GPS NMEA from
    the host USART1 (Signal K, chartplotter, multiplexer) instead of the
    internal u-blox module. Useful when the AIS unit is mounted in a
    location with poor sky visibility for the internal GPS.
    Default OFF — preserves stock behavior. Enable at runtime with the new
    'extgps on' terminal command; the setting persists in flash.
2026-04-30 chore: tag firmware as 4.4.1-extgps for identification
    Adds the '-extgps' suffix to FW_REV so $PAISYS reports
    '4.4.1-extgps' after flashing. Lets users distinguish at runtime
    whether they are running the patched firmware or stock.
    Note: maintainer may prefer to drop this commit before merging
    upstream and tag the version differently. Easy to revert.

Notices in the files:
latest/CAD/Board-11.9/transponder-11.9.1/transponder-11.9.1.kicad_pcb:
(c)2016-2024
latest/CAD/NMEA0183Breakout/Rev7.1/NMEA0183Adapter-7.1.kicad_pcb:
(c)2024 Maverick Labs LLC
latest/CAD/NMEA2000Breakout/Rev8.1/NMEA2000Adapter-8.1.kicad_pcb:
(c)2023 Maverick Labs LLC
parts and their libraries:
COPYRIGHT: Copyright (C) 2021 Ultra Librarian. All rights reserved.
